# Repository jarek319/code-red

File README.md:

# code-red
A bunch of cool displays thrown together

I was digging through my pile of spare parts and found a few displays I wanted to get up and running.

The simple board just arranges them all in a pleasing way. I have had some success getting them through their entire character set, but need to think about how to serialize the data for all these different devices...

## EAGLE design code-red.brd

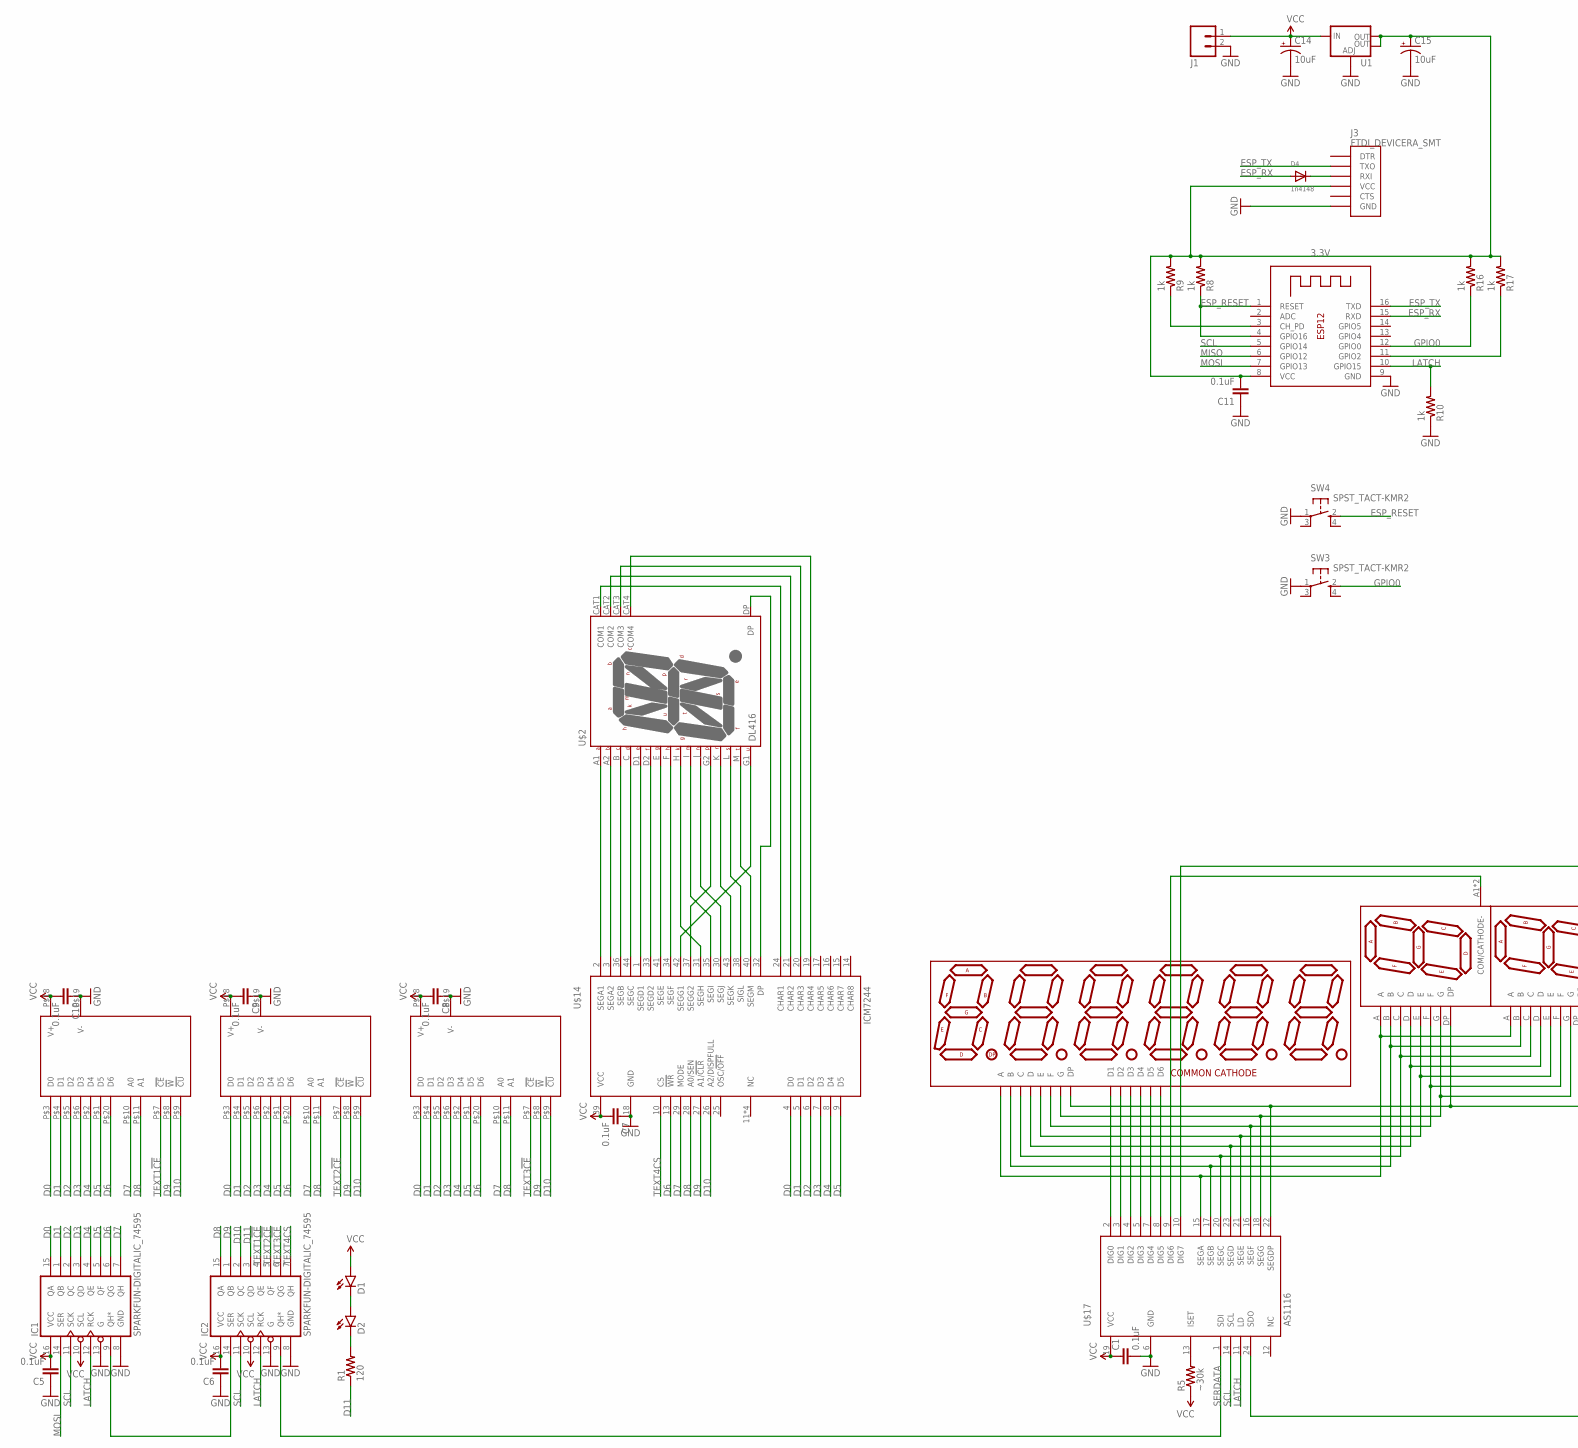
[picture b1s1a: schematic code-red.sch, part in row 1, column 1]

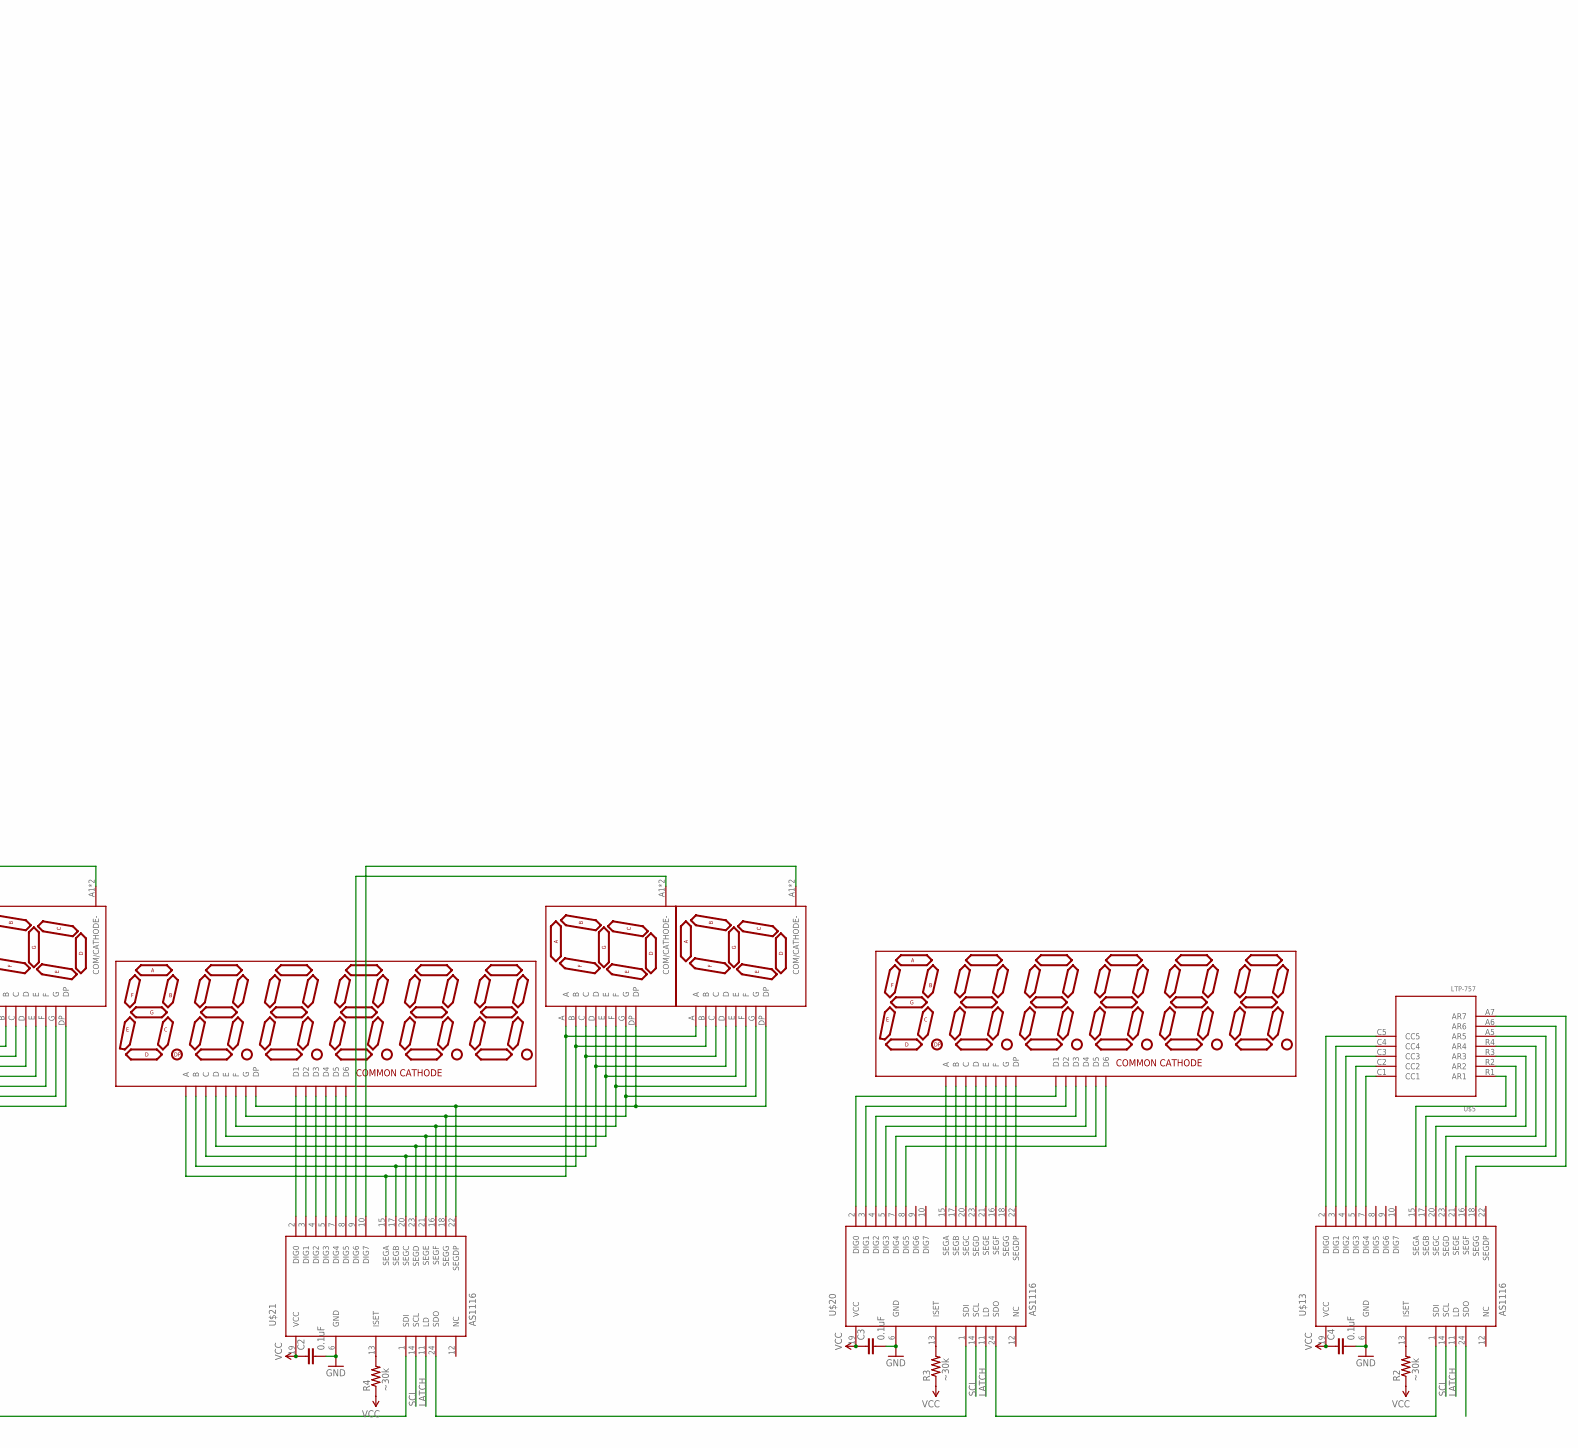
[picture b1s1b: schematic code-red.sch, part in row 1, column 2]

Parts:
C1, C2, C3, C4, C5, C6, C7, C8, C9, C10, C11: 0.1uF; 0805
C14, C15: 10uF; PANASONIC_D
D1, D2: LED3MM
D4: 1n4148; SOD-123
IC1, IC2: SPARKFUN-DIGITALIC_74595; SPARKFUN-DIGITALIC_TSSOP16
J1: M02LOCK_LONGPADS; 1X02_LOCK_LONGPADS
J3: FTDI_DEVICERA_SMT; FTDI_DEVICE_RA_SMT
R1: 120; 0805
R2, R3, R4, R5: ~30k; 0805
R8, R9, R10, R16, R17: 1k; 0805
SW3, SW4: SPST_TACT-KMR2; KMR2
U1: V_REG_LM1117SOT223; SOT223
U$1, U$6, U$7: DIS1291
U$2: DL416
U$3, U$8, U$9: DL1416T
U$4, U$10, U$11, U$12: FND259; FND359
U$5: LTP-757
U$13, U$17, U$20, U$21: AS1116; SSOP24
U$14: ICM7244; MQFP44-2
X1: ESP-12

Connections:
3.3V: C11.2, C15.+, J3.4 (VCC), R8.2, R9.2, R16.2, R17.2, U1.2 (OUT), U1.4 (OUT), X1.8 (VCC)
D0: IC1.15 (QA), U$3.P$3 (D0), U$8.P$3 (D0), U$9.P$3 (D0), U$14.4 (D0)
D1: IC1.1 (QB), U$3.P$4 (D1), U$8.P$4 (D1), U$9.P$4 (D1), U$14.5 (D1)
D2: IC1.2 (QC), U$3.P$5 (D2), U$8.P$5 (D2), U$9.P$5 (D2), U$14.6 (D2)
D3: IC1.3 (QD), U$3.P$6 (D3), U$8.P$6 (D3), U$9.P$6 (D3), U$14.7 (D3)
D4: IC1.4 (QE), U$3.P$2 (D4), U$8.P$2 (D4), U$9.P$2 (D4), U$14.8 (D4)
D5: IC1.5 (QF), U$3.P$1 (D5), U$8.P$1 (D5), U$9.P$1 (D5), U$14.9 (D5)
D6: IC1.6 (QG), U$3.P$20 (D6), U$8.P$20 (D6), U$9.P$20 (D6), U$14.13 (!WR)
D7: IC1.7 (QH), U$3.P$10 (A0), U$8.P$10 (A0), U$9.P$10 (A0), U$14.29 (MODE)
D8: IC2.15 (QA), U$3.P$11 (A1), U$8.P$11 (A1), U$9.P$11 (A1), U$14.28 (A0/SEN)
D9: IC2.1 (QB), U$3.P$8 (!W), U$8.P$8 (!W), U$9.P$8 (!W), U$14.27 (A1/!CLR)
D10: IC2.2 (QC), U$3.P$9 (!CU), U$8.P$9 (!CU), U$9.P$9 (!CU), U$14.26 (A2/DISPFULL)
D11: IC2.3 (QD), R1.1
ESP_RESET: R8.1, SW4.2 (S), X1.1 (RESET), X1.4 (GPIO16)
ESP_RX: D4.A, X1.15 (RXD)
ESP_TX: J3.2 (TXO), X1.16 (TXD)
GND: C1.2, C2.2, C3.2, C4.2, C5.1, C6.1, C7.1, C8.1, C9.1, C10.1, C11.1, C14.-, C15.-, IC1.8 (GND), IC1.13 (G), IC2.8 (GND), IC2.13 (G), J1.2, J3.6 (GND), R10.1, SW3.1, SW4.1, U1.1 (ADJ), U$3.P$19 (V-), U$8.P$19 (V-), U$9.P$19 (V-), U$13.6 (GND), U$14.18 (GND), U$17.6 (GND), U$20.6 (GND), U$21.6 (GND), X1.9 (GND)
GPIO0: R16.1, SW3.2 (S), X1.12 (GPIO0)
LATCH: IC1.12 (RCK), IC2.12 (RCK), R10.2, U$13.11 (LD), U$17.11 (LD), U$20.11 (LD), U$21.11 (LD), X1.10 (GPIO15)
MISO: X1.6 (GPIO12)
MOSI: IC1.14 (SER), X1.7 (GPIO13)
unnamed: U$1.P$12 (A), U$4.A, U$10.A, U$17.15 (SEGA)
unnamed: U$1.P$16 (F), U$4.F, U$10.F, U$17.16 (SEGF)
unnamed: U$1.P$15 (B), U$4.B, U$10.B, U$17.17 (SEGB)
unnamed: U$1.P$9 (G), U$4.G, U$10.G, U$17.18 (SEGG)
unnamed: U$1.P$1 (C), U$4.C, U$10.C, U$17.20 (SEGC)
unnamed: U$1.P$7 (E), U$4.E, U$10.E, U$17.21 (SEGE)
unnamed: U$1.P$8 (DP), U$4.DP, U$10.DP, U$17.22 (SEGDP)
unnamed: U$1.P$4 (D), U$4.D, U$10.D, U$17.23 (SEGD)
unnamed: U$1.P$14 (D1), U$17.2 (DIG0)
unnamed: U$1.P$3 (D2), U$17.3 (DIG1)
unnamed: U$1.P$13 (D3), U$17.4 (DIG2)
unnamed: U$1.P$5 (D4), U$17.5 (DIG3)
unnamed: U$1.P$11 (D5), U$17.7 (DIG4)
unnamed: U$1.P$6 (D6), U$17.8 (DIG5)
unnamed: U$6.P$12 (A), U$11.A, U$12.A, U$21.15 (SEGA)
unnamed: U$6.P$16 (F), U$11.F, U$12.F, U$21.16 (SEGF)
unnamed: U$6.P$15 (B), U$11.B, U$12.B, U$21.17 (SEGB)
unnamed: U$6.P$9 (G), U$11.G, U$12.G, U$21.18 (SEGG)
unnamed: U$6.P$1 (C), U$11.C, U$12.C, U$21.20 (SEGC)
unnamed: U$6.P$7 (E), U$11.E, U$12.E, U$21.21 (SEGE)
unnamed: U$6.P$8 (DP), U$11.DP, U$12.DP, U$21.22 (SEGDP)
unnamed: U$6.P$4 (D), U$11.D, U$12.D, U$21.23 (SEGD)
unnamed: U$6.P$14 (D1), U$21.2 (DIG0)
unnamed: U$6.P$3 (D2), U$21.3 (DIG1)
unnamed: U$6.P$13 (D3), U$21.4 (DIG2)
unnamed: U$6.P$5 (D4), U$21.5 (DIG3)
unnamed: U$6.P$11 (D5), U$21.7 (DIG4)
unnamed: U$6.P$6 (D6), U$21.8 (DIG5)
unnamed: U$7.P$12 (A), U$20.15 (SEGA)
unnamed: U$7.P$16 (F), U$20.16 (SEGF)
unnamed: U$7.P$15 (B), U$20.17 (SEGB)
unnamed: U$7.P$9 (G), U$20.18 (SEGG)
unnamed: U$7.P$1 (C), U$20.20 (SEGC)
unnamed: U$7.P$7 (E), U$20.21 (SEGE)
unnamed: U$7.P$8 (DP), U$20.22 (SEGDP)
unnamed: U$7.P$4 (D), U$20.23 (SEGD)
unnamed: U$7.P$14 (D1), U$20.2 (DIG0)
unnamed: U$7.P$3 (D2), U$20.3 (DIG1)
unnamed: U$7.P$13 (D3), U$20.4 (DIG2)
unnamed: U$7.P$5 (D4), U$20.5 (DIG3)
unnamed: U$7.P$11 (D5), U$20.7 (DIG4)
unnamed: U$7.P$6 (D6), U$20.8 (DIG5)
unnamed: U$2.G1 (U), U$14.42 (SEGG1)
unnamed: R2.2, U$13.13 (ISET)
unnamed: R3.2, U$20.13 (ISET)
unnamed: R4.2, U$21.13 (ISET)
unnamed: R5.2, U$17.13 (ISET)
unnamed: IC1.9 (QH*), IC2.14 (SER)
unnamed: U$2.CAT1 (COM1), U$14.24 (CHAR1)
unnamed: U$13.1 (SDI), U$20.24 (SDO)
unnamed: D1.K (C), D2.A
unnamed: D2.K (C), R1.2
unnamed: U$2.A1 (A), U$14.2 (SEGA1)
unnamed: U$5.C1 (CC1), U$13.7 (DIG4)
unnamed: U$5.C2 (CC2), U$13.5 (DIG3)
unnamed: U$5.C3 (CC3), U$13.4 (DIG2)
unnamed: U$5.C4 (CC4), U$13.3 (DIG1)
unnamed: U$5.C5 (CC5), U$13.2 (DIG0)
unnamed: U$5.R1 (AR1), U$13.15 (SEGA)
unnamed: U$5.R2 (AR2), U$13.17 (SEGB)
unnamed: U$5.R3 (AR3), U$13.20 (SEGC)
unnamed: U$5.R4 (AR4), U$13.23 (SEGD)
unnamed: U$5.A5 (AR5), U$13.21 (SEGE)
unnamed: U$5.A6 (AR6), U$13.16 (SEGF)
unnamed: U$5.A7 (AR7), U$13.18 (SEGG)
unnamed: U$2.B (C1), U$14.36 (SEGB)
unnamed: U$2.C (D), U$14.44 (SEGC)
unnamed: U$20.1 (SDI), U$21.24 (SDO)
unnamed: U$2.CAT2 (COM2), U$14.21 (CHAR2)
unnamed: U$2.CAT3 (COM3), U$14.20 (CHAR3)
unnamed: U$2.CAT4 (COM4), U$14.19 (CHAR4)
unnamed: U$17.24 (SDO), U$21.1 (SDI)
unnamed: U$2.A2 (B1), U$14.3 (SEGA2)
unnamed: U$2.D2 (F1), U$14.33 (SEGD2)
unnamed: U$2.E (G), U$14.41 (SEGE)
unnamed: U$2.F (H1), U$14.34 (SEGF)
unnamed: U$2.H (K1), U$14.31 (SEGH)
unnamed: U$2.I (M1), U$14.35 (SEGI)
unnamed: U$2.J (N), U$14.30 (SEGJ)
unnamed: U$2.K (R), U$14.43 (SEGK)
unnamed: U$2.L (S), U$14.38 (SIGL)
unnamed: U$2.M (T), U$14.40 (SEGM)
unnamed: U$2.D1 (E1), U$14.1 (SEGD1)
unnamed: U$2.DP, U$14.32 (DP)
unnamed: U$2.G2, U$14.37 (SEGG2)
unnamed: U$4.A1 (COM/CATHODE-), U$4.A2 (COM/CATHODE-), U$17.9 (DIG6)
unnamed: U$10.A1 (COM/CATHODE-), U$10.A2 (COM/CATHODE-), U$17.10 (DIG7)
unnamed: U$11.A1 (COM/CATHODE-), U$11.A2 (COM/CATHODE-), U$21.9 (DIG6)
unnamed: U$12.A1 (COM/CATHODE-), U$12.A2 (COM/CATHODE-), U$21.10 (DIG7)
unnamed: R9.1, X1.3 (CH_PD)
unnamed: D4.C, J3.3 (RXI)
unnamed: R17.1, X1.11 (GPIO2)
SCL: IC1.11 (SCK), IC2.11 (SCK), U$13.14 (SCL), U$17.14 (SCL), U$20.14 (SCL), U$21.14 (SCL), X1.5 (GPIO14)
SERDATA: IC2.9 (QH*), U$17.1 (SDI)
TEXT1!CE: IC2.4 (QE), U$3.P$7 (!CE)
TEXT2!CE: IC2.5 (QF), U$8.P$7 (!CE)
TEXT3!CE: IC2.6 (QG), U$9.P$7 (!CE)
TEXT4CS: IC2.7 (QH), U$14.10 (CS)
VCC: C1.1, C2.1, C3.1, C4.1, C5.2, C6.2, C7.2, C8.2, C9.2, C10.2, C14.+, D1.A, IC1.10 (SCL), IC1.16 (VCC), IC2.10 (SCL), IC2.16 (VCC), J1.1, R2.1, R3.1, R4.1, R5.1, U1.3 (IN), U$3.P$18 (V+), U$8.P$18 (V+), U$9.P$18 (V+), U$13.19 (VCC), U$14.39 (VCC), U$17.19 (VCC), U$20.19 (VCC), U$21.19 (VCC)

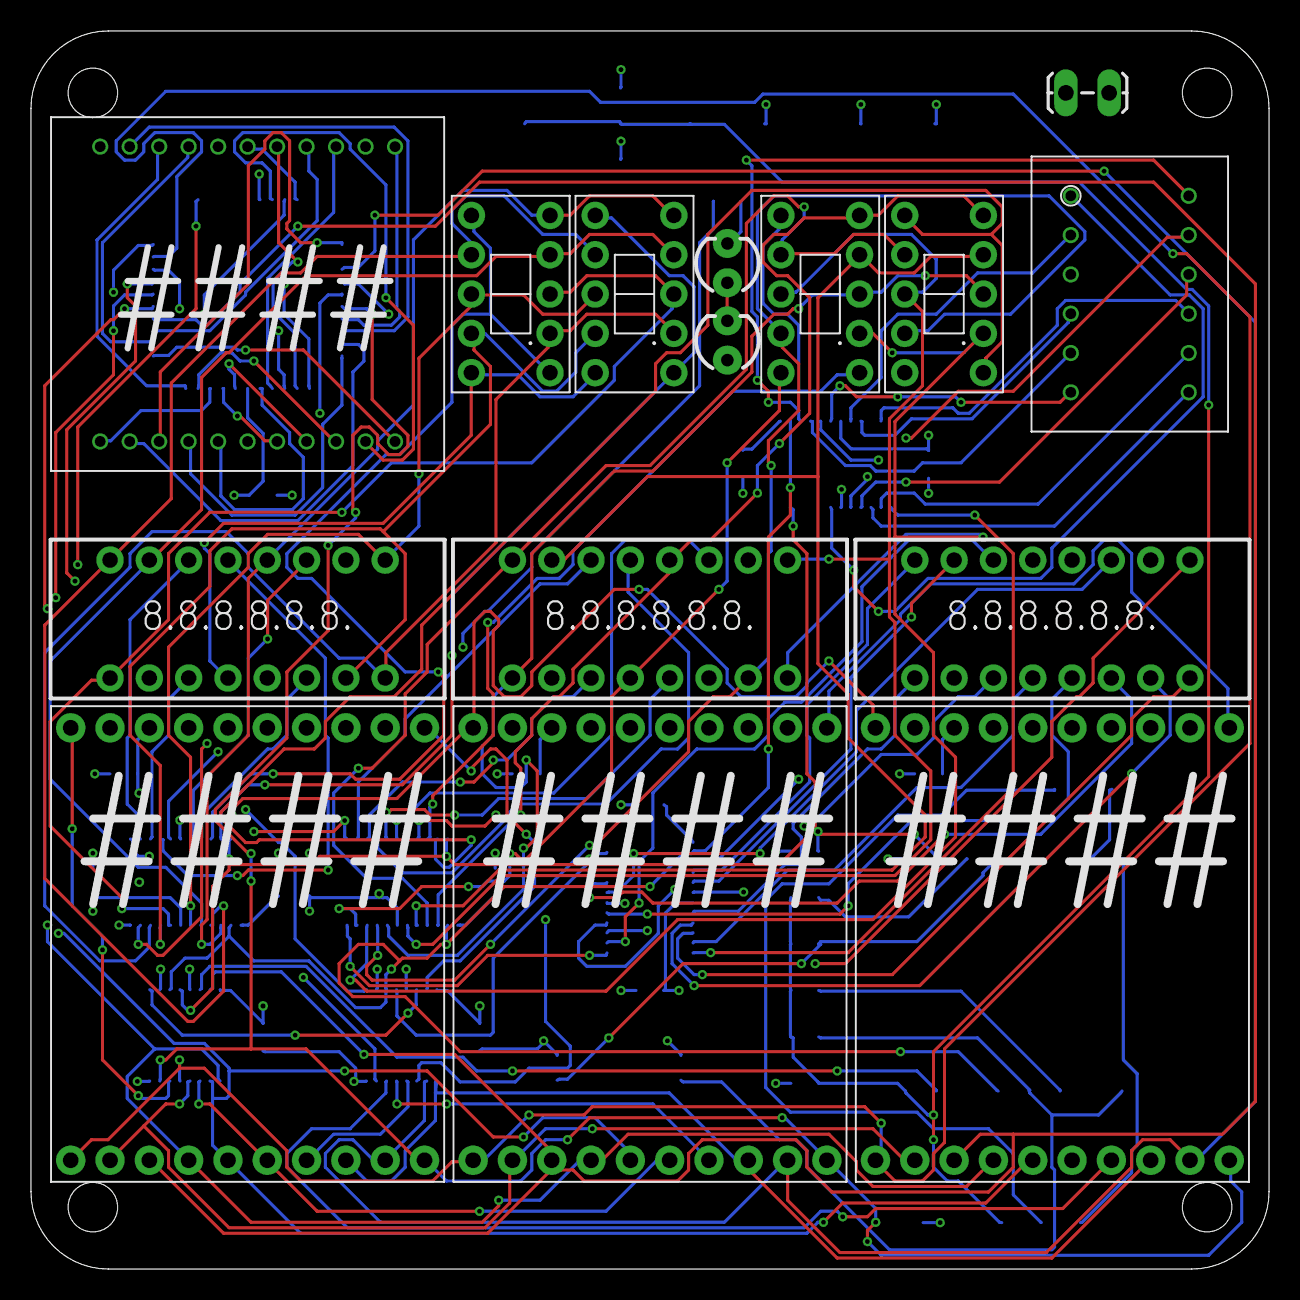
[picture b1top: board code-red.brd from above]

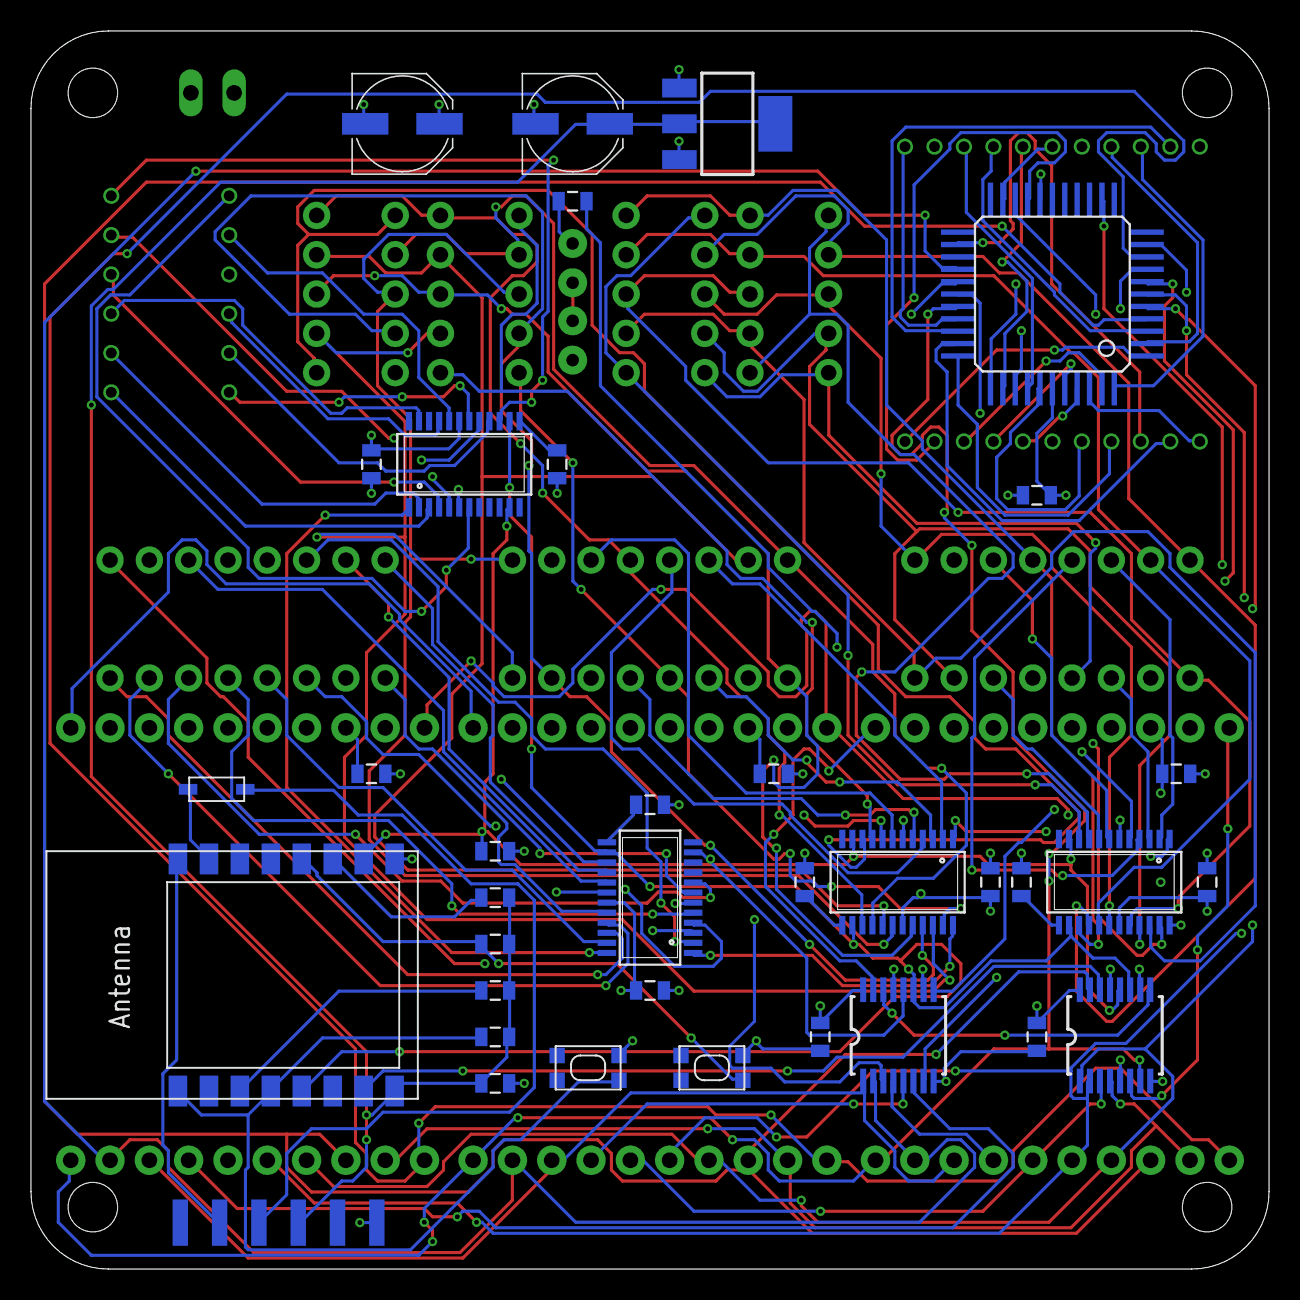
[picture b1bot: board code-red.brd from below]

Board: 4 copper layers, 80.0 x 80.0 mm, 51 parts (36 on the bottom side), 119 nets.

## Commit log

2018-07-05 design testing: needs programming

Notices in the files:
parts and their libraries:
SparkFun-LED: Licensing: Creative Commons ShareAlike 4.0 International - https://creativecommons.org/licenses/by-sa/4.0
